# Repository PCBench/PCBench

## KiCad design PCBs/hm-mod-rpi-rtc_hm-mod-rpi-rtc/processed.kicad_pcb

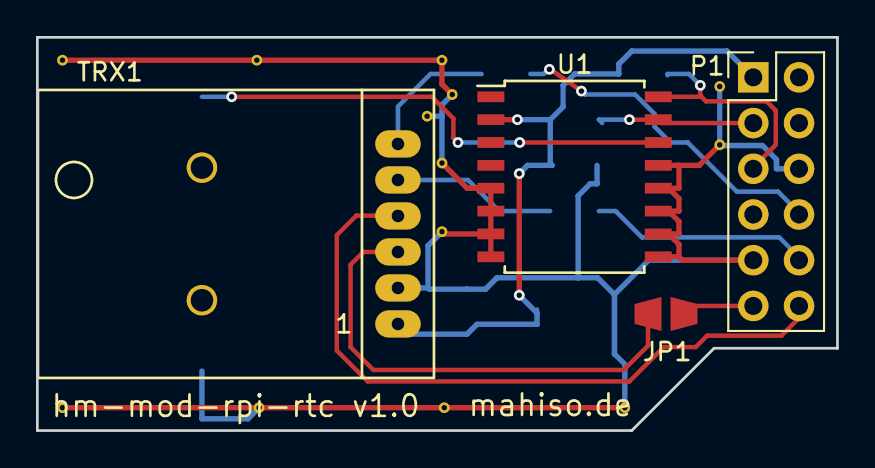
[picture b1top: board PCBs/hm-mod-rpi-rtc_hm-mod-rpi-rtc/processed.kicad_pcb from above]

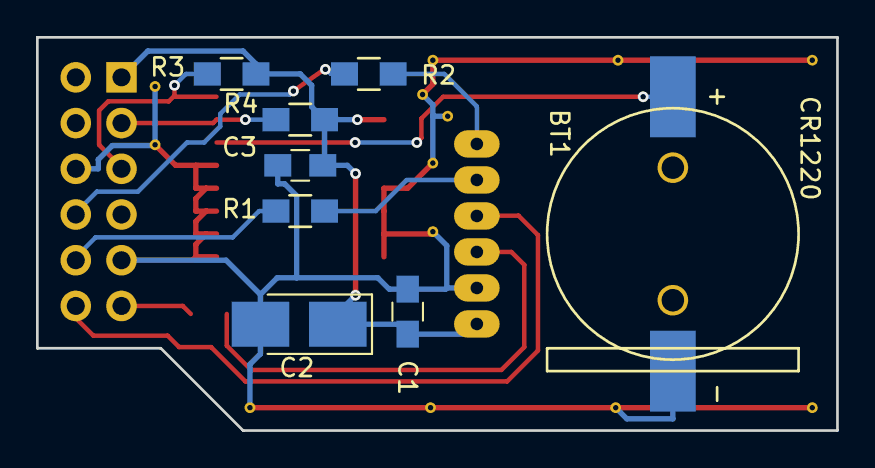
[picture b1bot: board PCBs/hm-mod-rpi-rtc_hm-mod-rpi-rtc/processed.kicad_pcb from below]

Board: 2 copper layers, 44.5 x 21.8 mm, 12 parts (8 on the bottom side), 12 nets.

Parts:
BT1: CR1220; CR1220_holder
C1, C3: 100n; C_0805_HandSoldering
C2: 100u/10V; CP_Tantalum_Case-B_EIA-3528-21_Hand
JP1: Prog; solder_jumper
P1: RPI CONN; Pin_Header_Straight_2x06_Pitch2.54mm
R1, R2: 1k; R_0805_HandSoldering
R3, R4: 4.7K; R_0805_HandSoldering
TRX1: HM-MOD-UART
U1: DS3231; SOIC-16W_7.5x10.3mm_Pitch1.27mm

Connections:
/PROG: JP1.1, P1.11
/RESET: P1.12, TRX1.4
/RX: P1.8, R2.1
/SCL: P1.5, R3.2, U1.16
/SDA: P1.3, R4.2, U1.15
/TX: P1.10, R1.1
GND: BT1.2, C1.2, C2.2, C3.2, P1.6, P1.9, TRX1.2, U1.5, U1.6, U1.7, U1.8, U1.9, U1.10, U1.11, U1.12, U1.13
unnamed: BT1.1, U1.14
unnamed: JP1.2, TRX1.3
unnamed: R1.2, TRX1.5
unnamed: R2.2, TRX1.6
VCC: C1.1, C2.1, C3.1, P1.1, R3.1, R4.1, TRX1.1, U1.2

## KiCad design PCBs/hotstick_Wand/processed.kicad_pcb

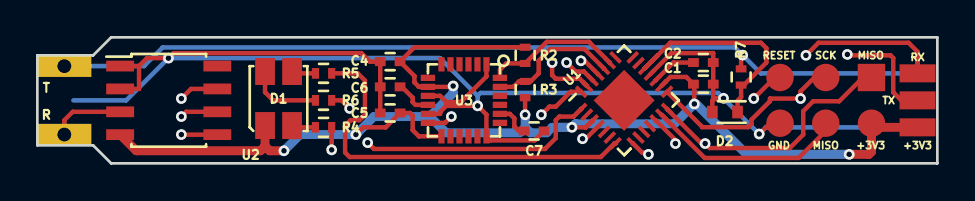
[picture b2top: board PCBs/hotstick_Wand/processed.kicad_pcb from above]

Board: 4 copper layers, 50.0 x 7.0 mm, 20 parts (1 on the bottom side), 24 nets.

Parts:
C1, C2, C4, C6: 100n; C_0402
C5: 10n; C_0402
C7: 2.2n; C_0402
D1: ASMB-MTB0-0A3A2; Tri-Colour_LED
D2: 3V3; SOD-523
P1: ISP; ISP_pads_2x3
P2: KLB4; Jack_3.5mm_KLB
P3: BASE; Base_Connector
R2, R3: 10k; R_0402
R4: 68R; R_0402
R5, R6: 10R; R_0402
R7: 10K; R_0402
U1: ATMEGA328-MMH; QFN-28-1EP_4x4mm_Pitch0.45mm
U2: MAX31855KASA+; SOIC-8_3.9x4.9mm_Pitch1.27mm
U3: MPU-6050

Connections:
+3V3: C1.1, C4.2, C5.2, D1.1, P1.2, P3.1, R2.1, R3.1, U1.3, U1.16, U2.4, U3.8, U3.13
/HEAT: P2.T, P3.2, R7.1
/HEAT_DETECT: D2.1, R7.2, U1.19
/LED_B: R6.1, U1.8
/LED_G: R5.1, U1.7
/LED_R: R4.1, U1.1
/MISO: P1.1, U1.14, U2.7
/MOSI: P1.4, U1.13
/MPU_INT: U1.28, U3.12
/RESET: P1.5, U1.25
/RX: P3.3, U1.26
/SCK: P1.3, U1.15, U2.5
/SCL: R3.2, U1.24, U3.23
/SDA: R2.2, U1.23, U3.24
/SENS: P2.R, U2.3
/TIP_TEMP_SELECT: U1.12, U2.6
/TX: P3.4, U1.27
GND: C1.2, C2.2, C4.1, C5.1, C6.1, C7.1, D2.2, P1.6, P2.S, P3.5, U1.4, U1.18, U2.1, U2.2, U3.1, U3.9, U3.11, U3.18
unnamed: C2.1, U1.17
unnamed: C6.2, U3.10
unnamed: C7.2, U3.20
unnamed: D1.2, R6.2
unnamed: D1.3, R5.2
unnamed: D1.4, R4.2

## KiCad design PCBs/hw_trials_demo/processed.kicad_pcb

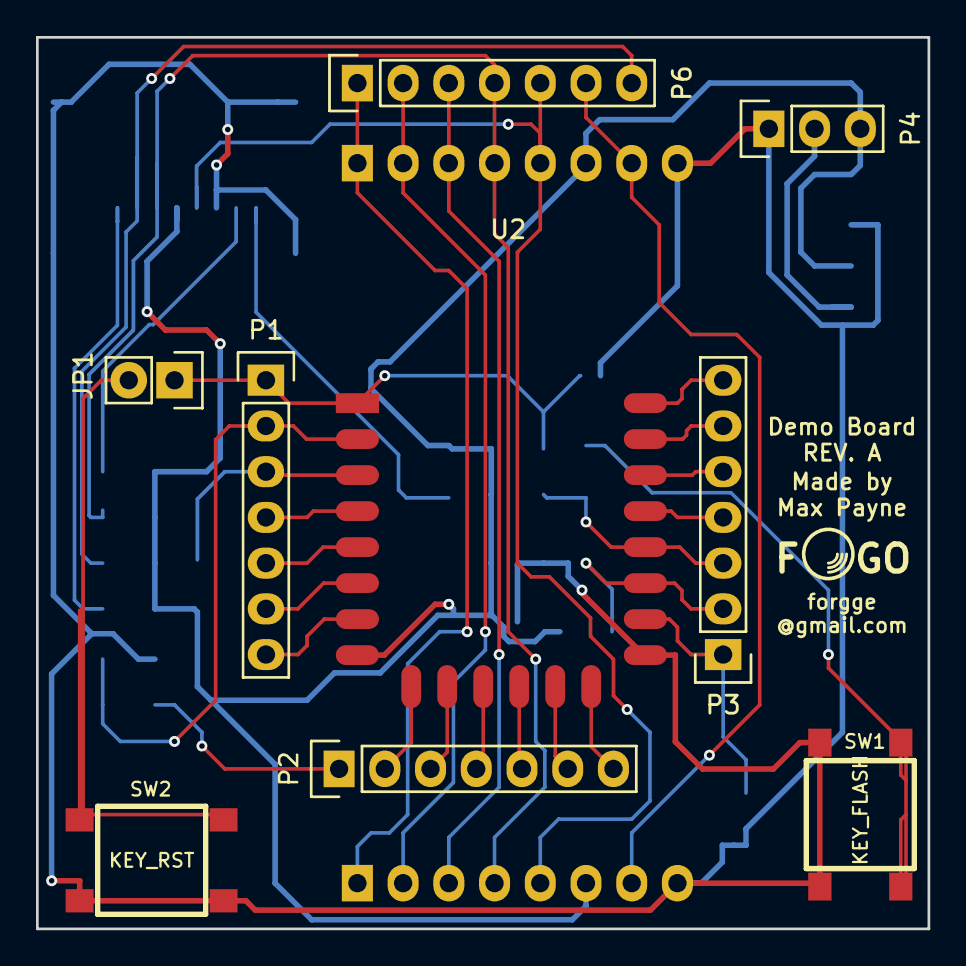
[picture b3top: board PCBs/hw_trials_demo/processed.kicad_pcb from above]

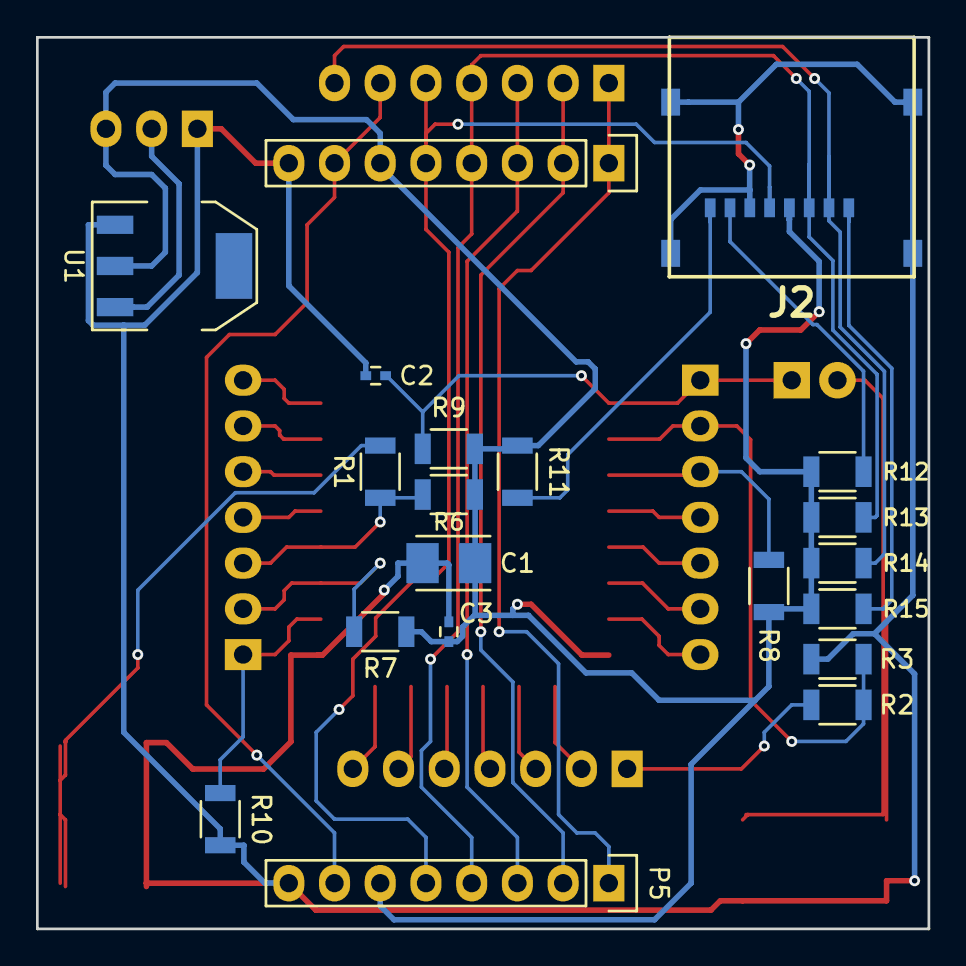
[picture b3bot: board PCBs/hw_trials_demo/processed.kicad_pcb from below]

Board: 2 copper layers, 49.5 x 49.5 mm, 28 parts (19 on the bottom side), 36 nets.

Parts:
C1: 100uF; TantalC_SizeB_EIA-3528_Reflow
C2: 100nF; C_0402
C3: 1nF; C_0402
J2: MICRO_SD_HINGE; MICRO_SD_HINGE_AMP
JP1: Jumper_NO_Small; Pin_Header_Straight_1x02
P1, P2, P3: ESP_CONN; Pin_Header_Straight_1x07
P4: PWR_CONN; Pin_Header_Straight_1x03
P5: CONN_DISPLAY; Nokia_5110_LCD
P6: SD_LCD_CONN; Pin_Header_Straight_1x07
R1: 470; R_1206
R2: 220k; R_1206
R3: 100k; R_1206
R6, R7, R8, R9, R10: 12k; R_1206
R11, R12, R13, R14, R15: 50k; R_1206
SW1: KEY_FLASH; SW_PUSH_SMD
SW2: KEY_RST; SW_PUSH_SMD
U1: NCP1117ST33T3G; SOT-223
U2: ESP-12E; ESP-12E_with_3d

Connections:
5V: P4.2, U1.3
/ADC: P1.2, R2.1, R3.2, U2.2
/ADC_EX: P2.1, R2.2
/EN: P1.3, R8.2, U2.3
/GPIO0: P3.3, R1.1, R6.2, U2.18
/GPIO2: P3.2, R7.2, U2.17
/GPIO4: P3.4, U2.19
/GPIO5: P3.5, U2.20
/GPIO9: P2.4, U2.11
/GPIO10: P2.5, U2.12
/GPIO12: P1.6, U2.6
/GPIO13: P1.7, U2.7
/GPIO14: P1.5, U2.5
/GPIO15: P3.1, R10.2, U2.16
/GPIO16: P1.4, U2.4
/LCD_CS: P5.2, P6.2
/LCD_LED: P5.7, P6.6
/LCD_RST: P5.1, P6.1
/RXD0: P3.6, U2.21
/SD_CS: J2.2, P6.7, R14.2
/SD_LCD_CLK: J2.5, P5.5, P6.5
/SD_LCD_DATA_CMD: P5.3, P6.3
/SD_LCD_MISO: J2.7, R12.2
/SD_LCD_MOSI: J2.3, P5.4, P6.4, R13.2
/SPI_CLK: P2.7, U2.14
/SPI_INT: P2.6, U2.13
/SPI_MISO: P2.3, U2.10
/SPI_MOSI: P2.2, U2.9
/TXD0: P3.7, U2.22
/nRST: C2.1, JP1.1, P1.1, R9.2, U2.1
GND: C1.2, C2.2, C3.2, J2.6, J2.9, J2.10, J2.11, J2.12, P4.1, P5.8, R3.1, R10.1, SW1.2, SW2.2, U1.1, U2.15
unnamed: J2.1, R15.2
unnamed: J2.8, R11.2
unnamed: JP1.2, SW2.1
unnamed: R1.2, SW1.1
VCC: C1.1, C3.1, J2.4, P4.3, P5.6, R6.1, R7.1, R8.1, R9.1, R11.1, R12.1, R13.1, R14.1, R15.1, U1.2, U2.8

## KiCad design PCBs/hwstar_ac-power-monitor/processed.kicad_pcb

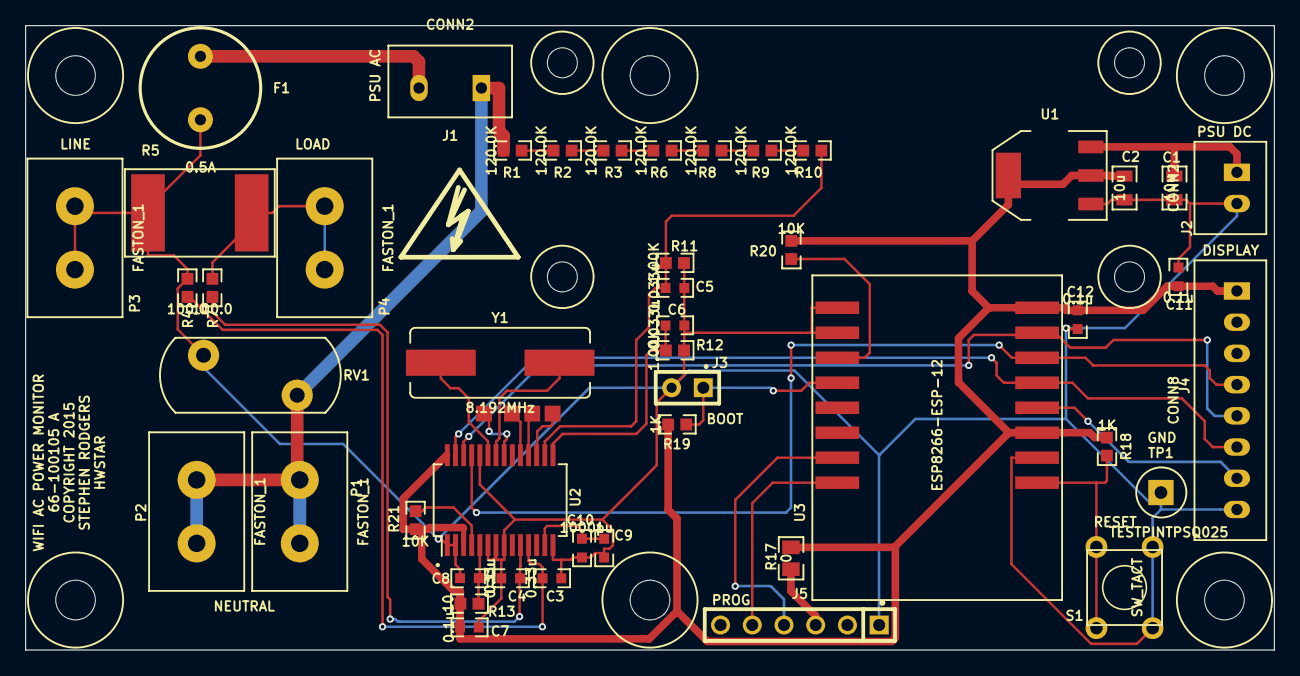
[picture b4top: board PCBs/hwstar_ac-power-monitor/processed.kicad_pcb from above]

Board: 2 copper layers, 100.0 x 50.0 mm, 62 parts (0 on the bottom side), 35 nets.

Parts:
C1, C2: 10u; CC0805
C3, C4: 0.33u; CC0603
C5, C6: 0.033u; CC0603
C7, C8, C11, C12: 0.1u; CC0603
C9: 1u; CC0603
C10: 1000p; CC0603
F1: 0.5A; BELFUSE_MRT
J1: CONN2; JST_B3B_SPECIAL
J2: CONN2; JST_B2B_XH_A
J3: CONN2; BERG2
J4: CONN8; JST_B8B_XH_A
J5: CONN6; BERG6
MTG-HOLE-125-RING-300, MTG-HOLE-125-RING-300_2, MTG-HOLE-125-RING-300_3, MTG-HOLE-125-RING-300_4, MTG-HOLE-125-RING-300_5, MTG-HOLE-125-RING-300_6: VAL**; MTG-HOLE-125-RING-300
MTG-HOLE-M2-RING-5MM, MTG-HOLE-M2-RING-5MM_2, MTG-HOLE-M2-RING-5MM_3, MTG-HOLE-M2-RING-5MM_4: VAL**; MTG-HOLE-M2-RING-5MM
P1, P2, P3, P4: FASTON_1; KEYSTONE_1287-ST
R1, R2, R3, R6, R8, R9, R10: 120.0K; RC0603
R4, R7: 100.0; RC0603
R5: 0.001; WSL3921
R11, R12: 1.00K; RC0603
R13: 10; RC0603
R17: 0; RC0805
R18, R19: 1K; RC0603
R20, R21: 10K; RC0603
RV1: MOV-10D431; VARISTOR-10D
S1: SW_TACT; SW_TACT_6MM
Sym: Symbol_HighVoltage_Type2_SilkTop_VerySmall
TP1: TESTPINTPSQ025; TESTPIN
TP2, TP3, TP4, TP5: TESTPINTPSQ025; TESTPAD
U1: AZ1117CH-3.3TRG1; SOT-223-SAR
U2: 90E24PYGI; SSOP28-SAR
U3: ESP8266-ESP-12; ESP8266-ESP12
Y1: 8.192MHz; HC49US-SAR

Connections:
+3.3V: C2.1, C7.1, C11.1, C12.1, J4.1, R13.1, R17.1, R18.1, R19.1, R20.1, R21.1, U1.2, U1.4, U2.3, U2.28, U3.3, U3.8
/Power/+5V: C1.1, J2.1, U1.3
/Power/HOT: F1.2, J1.2
/Power/LOAD: P4.1, P4.2, R5.2, R7.2
/Power/NEUTRAL: J1.1, P1.1, P1.2, P2.1, P2.2, R1.1, RV1.1
/WIFI/GPIO16: J4.7, U3.4
/WIFI/SPWR: J5.3, R17.2
GND: C1.2, C2.2, C3.2, C4.1, C5.2, C6.2, C7.2, C8.2, C9.2, C10.2, C11.2, C12.2, F1.1, J2.2, J3.2, J4.8, J5.1, P3.1, P3.2, R4.2, R5.1, R11.2, R12.2, RV1.2, S1.1, S1.2, TP1.1, U1.1, U2.1, U2.2, U2.6, U2.7, U2.8, U2.14, U2.24, U3.2, U3.9, U3.10
ISAMPLEN: C3.1, R4.1, U2.11
ISAMPLEP: C4.2, R7.1, U2.10
unnamed: C8.1, R13.2, U2.5
unnamed: C9.1, C10.1, U2.13
unnamed: J3.1, R19.2, U3.12
unnamed: J5.4, U3.15
unnamed: J5.5, U3.16
unnamed: R1.2, R2.1
unnamed: R2.2, R3.1
unnamed: R3.2, R6.1
unnamed: R6.2, R8.1
unnamed: R8.2, R9.1
unnamed: R9.2, R10.1
unnamed: R18.2, S1.3, S1.4, U3.1
unnamed: R20.2, U3.11
unnamed: R21.2, U2.4
unnamed: TP2.1, U2.18
unnamed: TP3.1, U2.19
unnamed: TP4.1, U2.21
unnamed: TP5.1, U2.17
unnamed: U2.22, Y1.2
unnamed: U2.23, Y1.1
SCLK: J4.4, U2.25, U3.6
SDI: J4.6, U2.27, U3.5
SDO: J4.5, U2.26, U3.7
VSAMPLEN: C6.1, R12.1, U2.15
VSAMPLEP: C5.1, R10.2, R11.1, U2.16

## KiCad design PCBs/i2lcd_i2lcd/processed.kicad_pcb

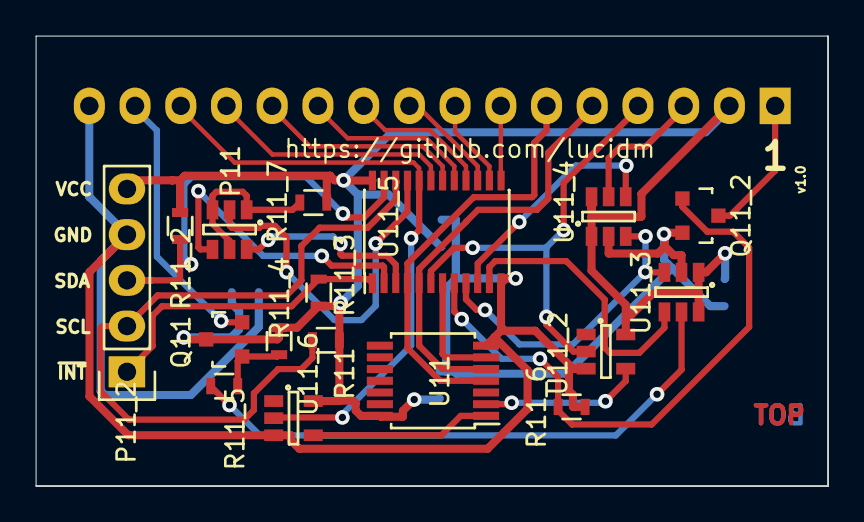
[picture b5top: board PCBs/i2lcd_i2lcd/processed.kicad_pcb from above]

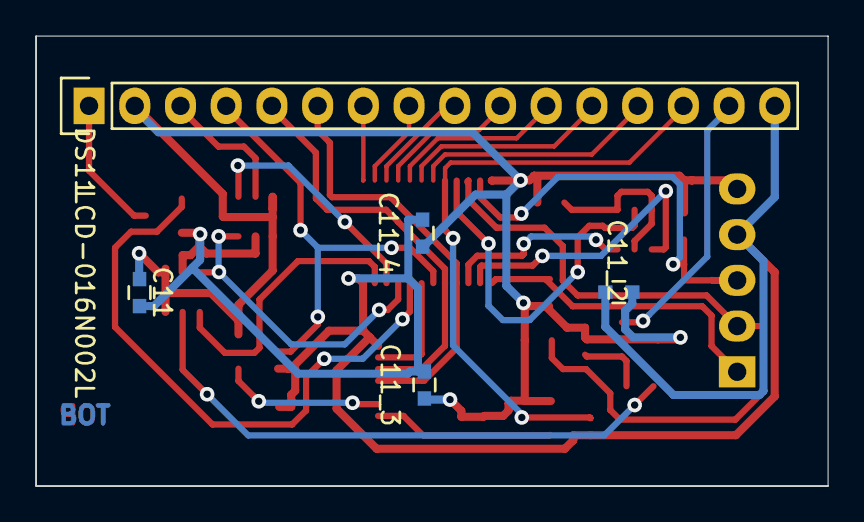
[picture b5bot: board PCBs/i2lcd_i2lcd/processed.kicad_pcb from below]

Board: 2 copper layers, 44.0 x 25.0 mm, 22 parts (5 on the bottom side), 32 nets.

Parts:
C11, C11_2, C11_3, C11_4: 100n; C_0603
DS11: LCD-016N002L; Pin_Header_Straight_1x16
P11: CONN_02X03; SOT-23-6
P11_2: CONN_01X05; Pin_Header_Straight_1x05
Q11: BT2N2222; SOT-23
Q11_2: IRLML6244; SOT-23
R11, R11_2, R11_3, R11_5: 4.7k; R_0603
R11_4: 220k; R_0603
R11_6: 100k; R_0603
R11_7: 47k; R_0603
U11: 74LS21; TSSOP-14_4.4x5mm_Pitch0.65mm
U11_2, U11_6: 74AHC1G14; SOT-23-5
U11_3, U11_4: MCP4013T-503; SOT-23-6
U11_5: PCA9535; TSSOP-24_4.4x7.8mm_Pitch0.65mm

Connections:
/D0: DS11.7, U11_5.13
/D1: DS11.8, U11_5.14
/D2: DS11.9, U11_5.15
/D3: DS11.10, U11_5.16
/D4: DS11.11, U11_5.17
/D5: DS11.12, U11_5.18
/D6: DS11.13, U11_5.19
A0: P11.2, U11_5.21
A1: P11.4, U11_5.2
A2: P11.6, U11_5.3
BRHT: R11_5.2, U11_3.5
D7: DS11.14, U11_5.20, U11_6.2
E: DS11.6, U11.4, U11_5.4
IRS: U11.6, U11_5.7
LED+: DS11.15, Q11.2
unnamed: DS11.1, Q11_2.3
unnamed: P11.1, P11.3, P11.5, R11_7.2
unnamed: Q11.1, R11_4.1, R11_5.1
unnamed: U11.2, U11_2.4
unnamed: U11.1, U11_6.4
PWR: Q11_2.1, R11_6.1, U11_5.8
R/~S: DS11.4, U11_2.2, U11_5.6
R/~W: DS11.5, U11.5, U11_5.5
SCL: P11_2.2, R11.1, U11_5.22
SDA: P11_2.3, R11_2.1, U11_5.23
U/~D: U11_3.3, U11_4.3, U11_5.9
VCC: C11.1, C11_2.1, C11_3.1, C11_4.1, DS11.2, P11_2.5, Q11.3, R11.2, R11_2.2, R11_3.1, R11_4.2, R11_7.1, U11.14, U11_2.5, U11_3.1, U11_3.6, U11_4.1, U11_4.6, U11_5.24, U11_6.5
VO: DS11.3, U11_4.5
Vss: C11.2, C11_2.2, C11_3.2, C11_4.2, DS11.16, P11_2.4, Q11_2.2, R11_6.2, U11.7, U11_2.3, U11_3.2, U11_4.2, U11_5.12, U11_6.3
~ACS: U11_4.4, U11_5.10
~BCS: U11_3.4, U11_5.11
~INT: P11_2.1, R11_3.2, U11_5.1

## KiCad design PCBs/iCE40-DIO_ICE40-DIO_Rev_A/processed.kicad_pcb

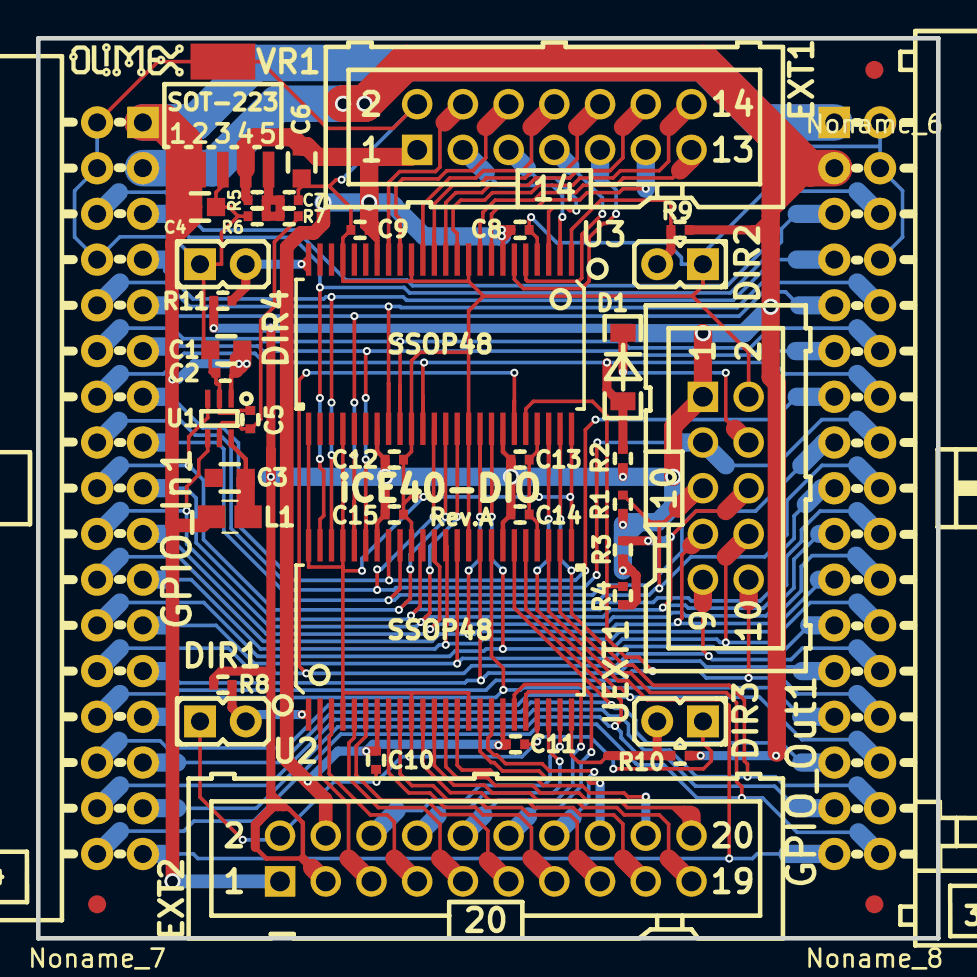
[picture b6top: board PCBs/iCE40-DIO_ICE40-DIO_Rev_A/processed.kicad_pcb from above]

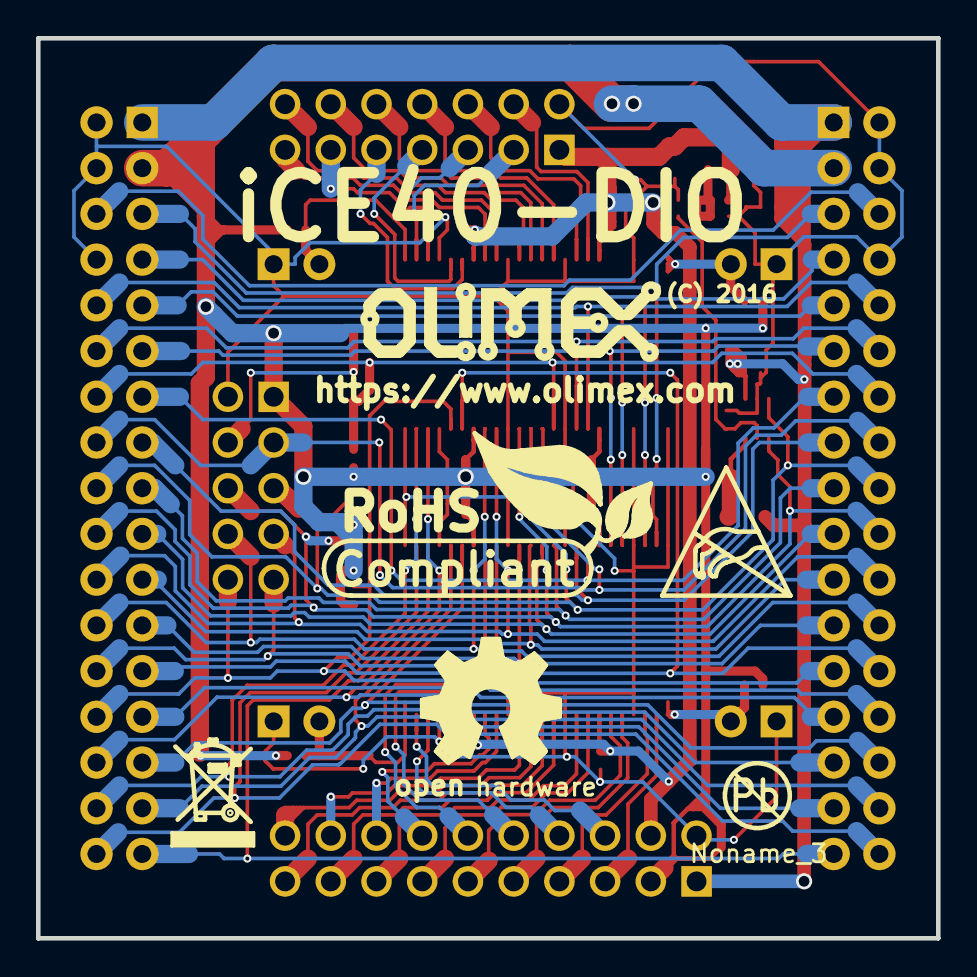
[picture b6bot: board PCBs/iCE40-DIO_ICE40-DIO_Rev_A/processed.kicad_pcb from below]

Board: 2 copper layers, 50.0 x 50.0 mm, 51 parts (6 on the bottom side), 69 nets.

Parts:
C1, C3, C4, C6: 22uF/6.3V/0603; C_0603_5MIL_DWS
C2, C5, C8, C9, C10, C11, C12, C13, C14, C15: 100nF; C_0402_5MIL_DWS
C7: NA(100nF); C_0402_5MIL_DWS
D1: 1N5819(S4SOD-123); SOD-123_1C-2A_KA
DIR1, DIR2, DIR3, DIR4: HN1x2(Opened); HN1x2
EXT1: BH14S
EXT2: BH20S
GPIO_In1: IDC34R; IDC34R_PCB
GPIO_Out1: BH34R
L1: FB0805/600R/2A; L_0805_5MIL_DWS
Noname_1: OLIMEX_LOGO_TB
Noname_2: LOGO_RECYCLEBIN_1
Noname_3: LOGO_PBFREE
Noname_4: LOGO_OPENHARDWARE_8x8
Noname_5: LOGO_OLIMEX_80
Noname_6, Noname_7, Noname_8: Fiducial1x3
R1, R3: 2.2k; R_0402_5MIL_DWS
R2, R4, R8, R9, R10, R11: 10k; R_0402_5MIL_DWS
R5, R7: 100k/1%; R_0402_5MIL_DWS
R6: 10k/1%; R_0402_5MIL_DWS
Ref**: Val**; LOGO_ROHS_1
Ref**_2: Val**; LOGO_ANTISTATIC_1
U1: MCP47A1T-A0E/LT(SC70-6); SC70-6_Pitch-0.65_2.00x2.10x1.00mm
U2, U3: 74ALVC164245DL(SSOP48); SSOP48_Pitch-0.635_16.00x10.40x2.80mm
UEXT1: BH10S
VR1: MCP1825-ADJE/DC(SOT-223-5); SOT-223-5_Pitch-1.27_6.50x7.00x1.80

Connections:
+3V3: C12.2, C13.2, C14.2, C15.2, EXT2.3, GPIO_In1.3, GPIO_Out1.3, R1.1, R2.1, R3.1, R4.1, R8.1, R9.1, R10.1, R11.1, U2.31, U2.42, U3.31, U3.42, UEXT1.1
+5V: C1.2, C2.2, C4.2, EXT2.1, GPIO_In1.1, GPIO_Out1.1, L1.2, U1.1, VR1.1, VR1.2
/EXTCLK: GPIO_In1.6, GPIO_Out1.6
/GPIO_Pin<5>: GPIO_In1.5, GPIO_Out1.5, U2.47
/GPIO_Pin<7>: GPIO_In1.7, GPIO_Out1.7, U2.46
/GPIO_Pin<9>: GPIO_In1.9, GPIO_Out1.9, U2.44
/GPIO_Pin<10>: GPIO_In1.10, GPIO_Out1.10, U3.32
/GPIO_Pin<11>: GPIO_In1.11, GPIO_Out1.11, U2.43
/GPIO_Pin<12>: GPIO_In1.12, GPIO_Out1.12, U3.33
/GPIO_Pin<13>: GPIO_In1.13, GPIO_Out1.13, U2.41
/GPIO_Pin<15>: GPIO_In1.15, GPIO_Out1.15, U2.40
/GPIO_Pin<17>: GPIO_In1.17, GPIO_Out1.17, U2.38
/GPIO_Pin<19>: GPIO_In1.19, GPIO_Out1.19, U2.37
/GPIO_Pin<21>: GPIO_In1.21, GPIO_Out1.21, U2.36
/GPIO_Pin<23>: GPIO_In1.23, GPIO_Out1.23, U2.35
/GPIO_Pin<25>: GPIO_In1.25, GPIO_Out1.25, U2.33
/GPIO_Pin<27>: GPIO_In1.27, GPIO_Out1.27, U2.32
/GPIO_Pin<29>: GPIO_In1.29, GPIO_Out1.29, U2.30
/GPIO_Pin<30>: GPIO_In1.30, GPIO_Out1.30, U3.46
/GPIO_Pin<31>: GPIO_In1.31, GPIO_Out1.31, U2.29
/GPIO_Pin<32>: GPIO_In1.32, GPIO_Out1.32, U3.47
/GPIO_Pin<33>: GPIO_In1.33, GPIO_Out1.33, U2.27
/GPIO_Pin<34>: GPIO_In1.34, GPIO_Out1.34, U2.26
/IO00: EXT2.5, U2.2
/IO01: EXT2.7, U2.3
/IO02: EXT2.9, U2.5
/IO03: EXT2.11, U2.6
/IO04: EXT2.13, U2.8
/IO05: EXT2.15, U2.9
/IO06: EXT2.17, U2.11
/IO07: EXT2.19, U2.12
/IO08: EXT2.20, U2.13
/IO09: EXT2.18, U2.14
/IO10: EXT2.16, U2.16
/IO11: EXT2.14, U2.17
/IO12: EXT2.12, U2.19
/IO13: EXT2.10, U2.20
/IO14: EXT2.8, U2.22
/IO15: EXT2.6, U2.23
/IO16: EXT1.3, U3.2
/IO17: EXT1.5, U3.3
/IO18: EXT1.7, U3.5
/IO19: EXT1.9, U3.6
/IO20: EXT1.11, U3.8
/IO21: EXT1.13, U3.9
/IO22: EXT1.14, U3.11
/IO23: EXT1.12, U3.12
/IO24: EXT1.10, U3.13
/IO25: EXT1.8, U3.14
/IO26: EXT1.6, U3.16
/IO27: EXT1.4, U3.17
/UEXT_#SS: GPIO_In1.28, GPIO_Out1.28, R4.2, U3.44, UEXT1.10
/UEXT_MISO: GPIO_In1.22, GPIO_Out1.22, U3.40, UEXT1.7
/UEXT_MOSI: GPIO_In1.24, GPIO_Out1.24, U3.41, UEXT1.8
/UEXT_RxD: D1.2, GPIO_In1.14, GPIO_Out1.14, R2.2, U3.35
/UEXT_SCK: GPIO_In1.26, GPIO_Out1.26, U3.43, UEXT1.9
/UEXT_SCL: GPIO_In1.18, GPIO_Out1.18, R1.2, U1.3, U3.37, UEXT1.5
/UEXT_SDA: GPIO_In1.20, GPIO_Out1.20, R3.2, U1.4, U3.38, UEXT1.6
/UEXT_TxD: GPIO_In1.16, GPIO_Out1.16, U3.36, UEXT1.3
/Vdac: C5.2, R7.2, U1.5
GND: C1.1, C2.1, C4.1, C5.1, C6.1, C7.1, C8.1, C9.1, C10.1, C11.1, C12.1, C13.1, C14.1, C15.1, DIR1.1, DIR2.1, DIR3.1, DIR4.1, EXT1.2, EXT2.2, GPIO_In1.2, GPIO_In1.4, GPIO_In1.8, GPIO_Out1.2, GPIO_Out1.4, GPIO_Out1.8, R6.1, U1.2, U2.4, U2.10, U2.15, U2.21, U2.25, U2.28, U2.34, U2.39, U2.45, U2.48, U3.4, U3.10, U3.15, U3.21, U3.25, U3.28, U3.34, U3.39, U3.45, U3.48, UEXT1.2, VR1.3, VR1.6
unnamed: C3.2, L1.1, U1.6
unnamed: C7.2, R5.2, R6.2, R7.1, VR1.5
unnamed: D1.1, UEXT1.4
unnamed: DIR1.2, R8.2, U2.1
unnamed: DIR2.2, R9.2, U3.1
unnamed: DIR3.2, R10.2, U2.24
unnamed: DIR4.2, R11.2, U3.24
VDD: C6.2, C8.2, C9.2, C10.2, C11.2, EXT1.1, EXT2.4, R5.1, U2.7, U2.18, U3.7, U3.18, VR1.4

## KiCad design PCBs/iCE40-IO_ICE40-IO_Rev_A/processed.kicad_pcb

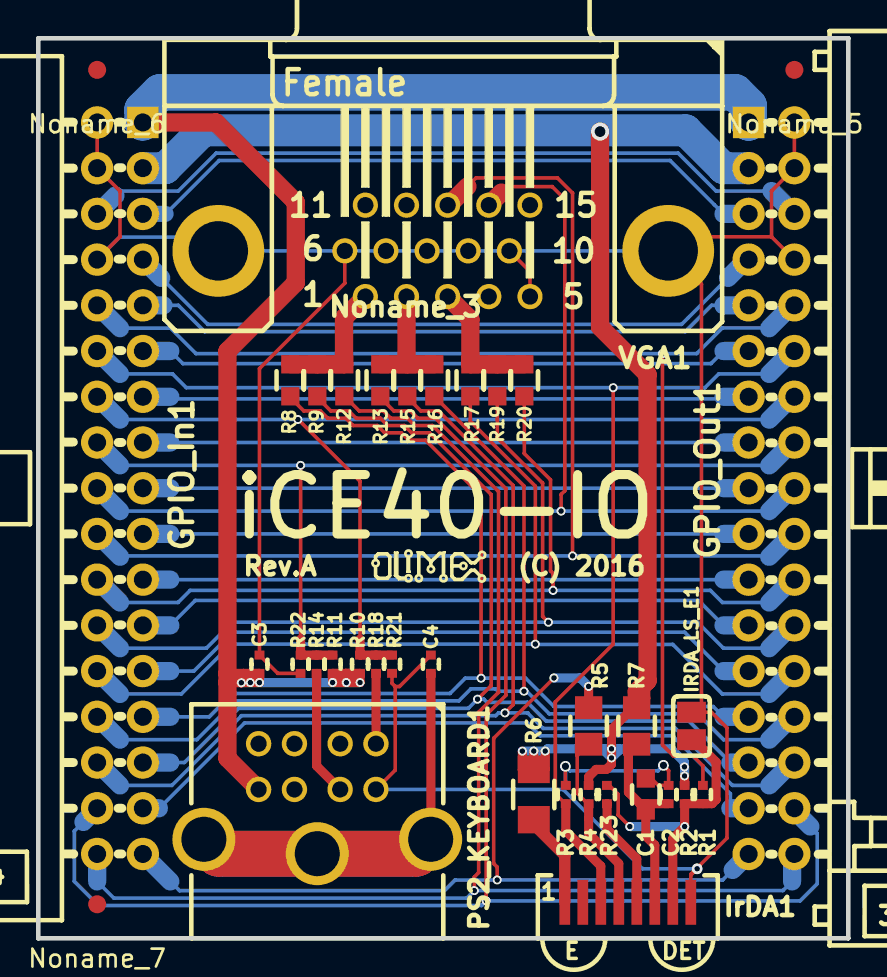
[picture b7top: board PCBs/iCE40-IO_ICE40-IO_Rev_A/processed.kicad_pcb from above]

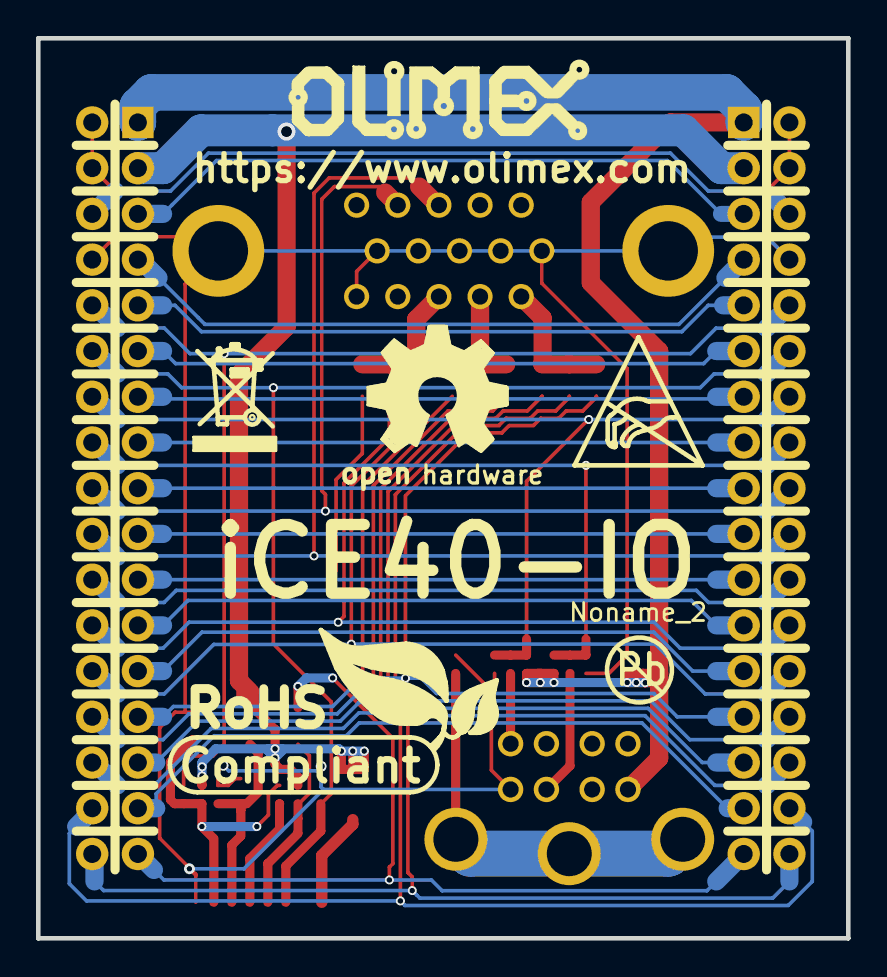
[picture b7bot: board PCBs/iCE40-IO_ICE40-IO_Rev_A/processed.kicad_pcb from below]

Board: 2 copper layers, 45.0 x 50.0 mm, 43 parts (6 on the bottom side), 43 nets.

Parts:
C1: 22uF/6.3V; C_0603_5MIL_DWS
C2, C3: 100nF; C_0402_5MIL_DWS
C4: 10nF; C_0402_5MIL_DWS
GPIO_In1: IDC34R; IDC34R_PCB
GPIO_Out1: BH34R
IRDA_LS_E1: Opened; SJ
IrDA1: TFDU4100; TFDU4100_PACK
Noname_1: LOGO_RECYCLEBIN_1
Noname_2: LOGO_PBFREE
Noname_3: OLIMEX_LOGO_SMALL_TB
Noname_4: OLIMEX_LOGO_TB
Noname_5, Noname_6, Noname_7: Fiducial1x3
Noname_8: LOGO_OPENHARDWARE_8x8
PS2_KEYBOARD1: MDR6_MINI-DIN; PS2_MDR6_MINI-DIN
R1, R4, R23: NA; R_0402_5MIL_DWS
R2, R21, R22: 10k; R_0402_5MIL_DWS
R3: NA(10k); R_0402_5MIL_DWS
R5, R7: 47R; R_0805_5MIL_DWS
R6: 15R; R_1206_5MIL_DWS
R8, R13, R17: 470R; C_0603_5MIL_DWS
R9, R15, R19: 1k; C_0603_5MIL_DWS
R10, R11: 5.6k; R_0402_5MIL_DWS
R12, R16, R20: 1.8k; C_0603_5MIL_DWS
R14, R18: 200R; R_0402_5MIL_DWS
Ref**: Val**; LOGO_ANTISTATIC_1
Ref**_2: Val**; LOGO_ROHS_1
VGA1: VGA15-F(CD0515S21J0)

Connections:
+3V3: GPIO_In1.3, GPIO_Out1.3, R2.2, R4.2, R6.2, R7.2
+5V: C3.2, GPIO_In1.1, GPIO_Out1.1, PS2_KEYBOARD1.4, R10.1, R11.1
/EXTCLK: GPIO_In1.6, GPIO_Out1.6
/GPIO_Pin<5>: GPIO_In1.5, GPIO_Out1.5
/GPIO_Pin<7>: GPIO_In1.7, GPIO_Out1.7
/GPIO_Pin<9>: GPIO_In1.9, GPIO_Out1.9
/GPIO_Pin<11>: GPIO_In1.11, GPIO_Out1.11
/GPIO_Pin<13>: GPIO_In1.13, GPIO_Out1.13
/GPIO_Pin<15>: GPIO_In1.15, GPIO_Out1.15
/GPIO_Pin<17>: GPIO_In1.17, GPIO_Out1.17
/GPIO_Pin<19>: GPIO_In1.19, GPIO_Out1.19
/GPIO_Pin<21>: GPIO_In1.21, GPIO_Out1.21
/GPIO_Pin<23>: GPIO_In1.23, GPIO_Out1.23
/GPIO_Pin<25>: GPIO_In1.25, GPIO_Out1.25
/GPIO_Pin<31>: GPIO_In1.31, GPIO_Out1.31
/IrDA_Rx: GPIO_In1.12, GPIO_Out1.12, IrDA1.3, R3.1
/IrDA_SC: GPIO_In1.10, GPIO_Out1.10, R1.1
/IrDA_Tx: GPIO_In1.33, GPIO_Out1.33, R5.1
/PS2_CLK: GPIO_In1.14, GPIO_Out1.14, R10.2, R18.1, R21.1
/PS2_DATA: GPIO_In1.16, GPIO_Out1.16, R11.2, R14.1, R22.1
/VGA_BLUE1: GPIO_In1.26, GPIO_Out1.26, R17.1
/VGA_BLUE2: GPIO_In1.24, GPIO_Out1.24, R19.1
/VGA_BLUE3: GPIO_In1.22, GPIO_Out1.22, R20.1
/VGA_GREEN1: GPIO_In1.32, GPIO_Out1.32, R13.1
/VGA_GREEN2: GPIO_In1.30, GPIO_Out1.30, R15.1
/VGA_GREEN3: GPIO_In1.28, GPIO_Out1.28, R16.1
/VGA_HSYNC: GPIO_In1.20, GPIO_Out1.20, VGA1.13
/VGA_RED1: GPIO_In1.27, GPIO_Out1.27, R8.1
/VGA_RED2: GPIO_In1.29, GPIO_Out1.29, R9.1
/VGA_RED3: GPIO_In1.34, GPIO_Out1.34, R12.1
/VGA_VSYNC: GPIO_In1.18, GPIO_Out1.18, VGA1.14
GND: C1.1, C2.1, C3.1, C4.1, GPIO_In1.2, GPIO_In1.4, GPIO_In1.8, GPIO_Out1.2, GPIO_Out1.4, GPIO_Out1.8, IRDA_LS_E1.2, IrDA1.8, PS2_KEYBOARD1.3, R3.2, R21.2, R22.2, VGA1.5, VGA1.6, VGA1.7, VGA1.8, VGA1.9, VGA1.10, VGA1.16, VGA1.17
unnamed: C1.2, C2.2, IrDA1.6, R7.1
unnamed: C4.2, PS2_KEYBOARD1.9
unnamed: IRDA_LS_E1.1, IrDA1.7, R1.2, R2.1, R23.2
unnamed: IrDA1.1, R6.1
unnamed: IrDA1.4, R4.1, R5.2
unnamed: IrDA1.5, R23.1
unnamed: PS2_KEYBOARD1.1, R14.2
unnamed: PS2_KEYBOARD1.5, R18.2
unnamed: R8.2, R9.2, R12.2, VGA1.1
unnamed: R13.2, R15.2, R16.2, VGA1.2
unnamed: R17.2, R19.2, R20.2, VGA1.3

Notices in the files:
PCBs/hwstar_ac-power-monitor/processed.kicad_pcb:
COPYRIGHT 2015
PCBs/iCE40-DIO_ICE40-DIO_Rev_A/processed.kicad_pcb:
(C) 2016
